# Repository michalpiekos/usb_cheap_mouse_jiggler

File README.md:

# Cheap mouse jiggler on USB
Simple USB-HID Mouse device on: STM32F103 (bluepill), CH32V003 (10cent RiscV processor).

Idea is to find cheap microcontroller with minimum external components to build mouse jiggler. I am sure no one needs such comparison therefore... here it is. Aliexpress can do it for around 2-2.5$ for ready made USB dongle. I wonder if I can beat that price. I will calculate the price of finished product including PCB, all components like usb plug or socket, resistors, capacitors, crystals, power regulators and what have you. In case of complete boards the price will be the price. I do not calculate shipping costs and USB cable if needed.

1. <b>STM32F103</b> Bluepill<br>The cheapest one I found on aliexpress was for 1.94$ and the price of shipping was reasonable. Mouse jiggler is implemented using STM HAL and it is super easy, especially using CubeIDE or CubeMX environments. Cheap and popular bluepill is then the benchmark in this small test.

2. <b>CH32V003</b> the 0.10$ RiscV microcontroller<br> Already a strong contender. One would need to create its own PCB. I used slightly changed version of the one that cnlohr posted on his github: https://github.com/cnlohr/rv003usb. <br> 
<b>Pricing: </b>0.23$ for chip and that only when buying 50pcs, 0.62$ for PCB (at least that is my price at one of chinese manufacturers),  LDO was 0.04$ and I will add 0.12$ for capacitors and resistor and 0.08$ for USB male connector. That totals <b>1.09$</b>. <br>
Probably a winner at this point. 

## CH32V003 Schematics
Provided here is my early breadboard prototype and PCB which I have ordered at one of chinese manufacturers.<br>
 <br>
Prototype does work:<br>
 <br>
PCB 3D view<br>
 <br>

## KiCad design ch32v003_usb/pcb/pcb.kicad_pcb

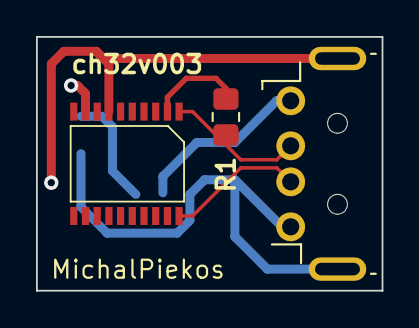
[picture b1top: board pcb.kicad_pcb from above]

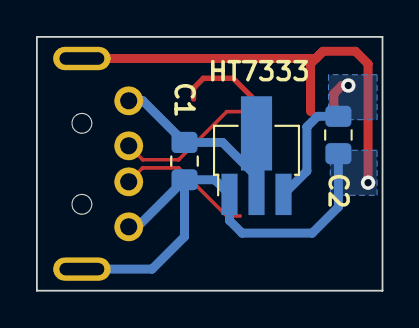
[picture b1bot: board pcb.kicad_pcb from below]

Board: 2 copper layers, 19.2 x 14.1 mm, 6 parts (3 on the bottom side), 6 nets.

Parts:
C1, C2: 10u; C_0805_2012Metric_Pad1.18x1.45mm_HandSolder
J1: USB_A; USB_A_Horizontal
R1: 1k5; R_0805_2012Metric_Pad1.20x1.40mm_HandSolder
U1: HT7333; SOT-89-3_Handsoldering
ch32v003f4p6: SSOP-20_4.4x6.5mm_P0.65mm

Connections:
+3.3V: C2.1, U1.3 (VOUT), ch32v003f4p6.9 (VDD)
+5V: C1.1, J1.1 (VBUS), U1.2 (VIN)
/DPU: R1.1, ch32v003f4p6.2 (PD5/A5/UTX/T2CH4_/URX_)
/USB_D+: J1.3 (D+), ch32v003f4p6.20 (PD3/A4/T2CH2/AETR/UCTS/T1CH4_)
/USB_D-: J1.2 (D-), R1.2, ch32v003f4p6.1 (PD4/A7/UCK/T2CH1ETR/OPO/T1CH4ETR_)
GND: C1.2, C2.2, J1.4 (GND), J1.5 (Shield), U1.1 (GND), ch32v003f4p6.7 (VSS)
